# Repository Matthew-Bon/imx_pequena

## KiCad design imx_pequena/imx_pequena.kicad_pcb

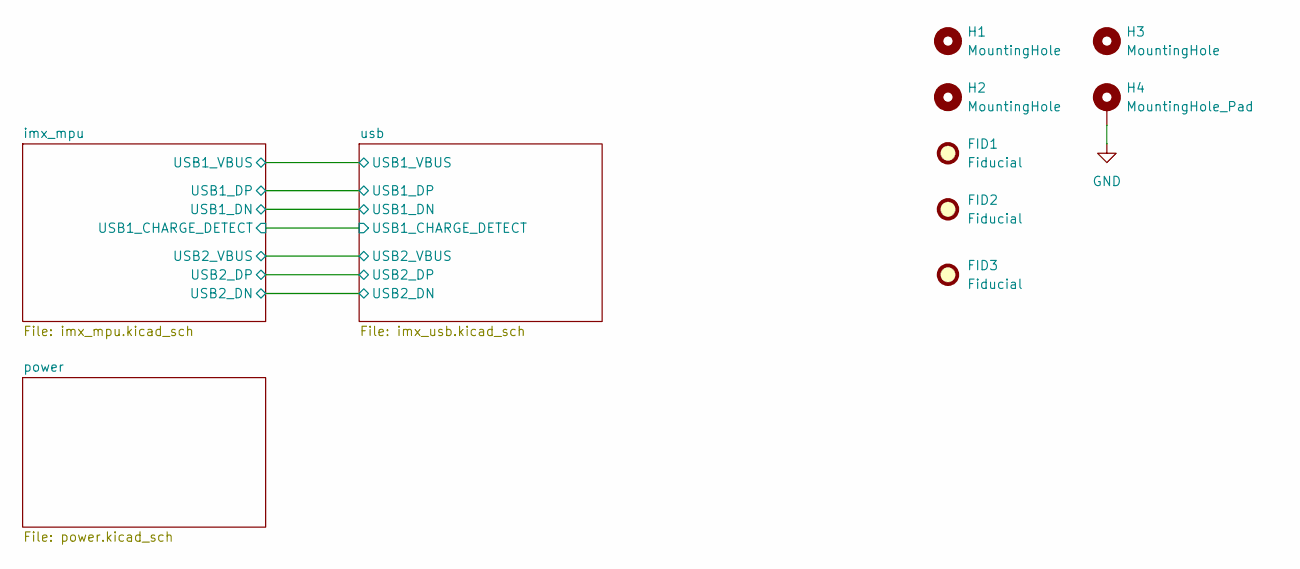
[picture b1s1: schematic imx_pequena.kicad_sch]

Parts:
FID1, FID2, FID3: Fiducial; Fiducial_1mm_Mask2mm
H1, H2, H3: MountingHole; MountingHole_2.5mm
H4: MountingHole_Pad; MountingHole_2.5mm_Pad

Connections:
GND: H4.1; also elsewhere on the board

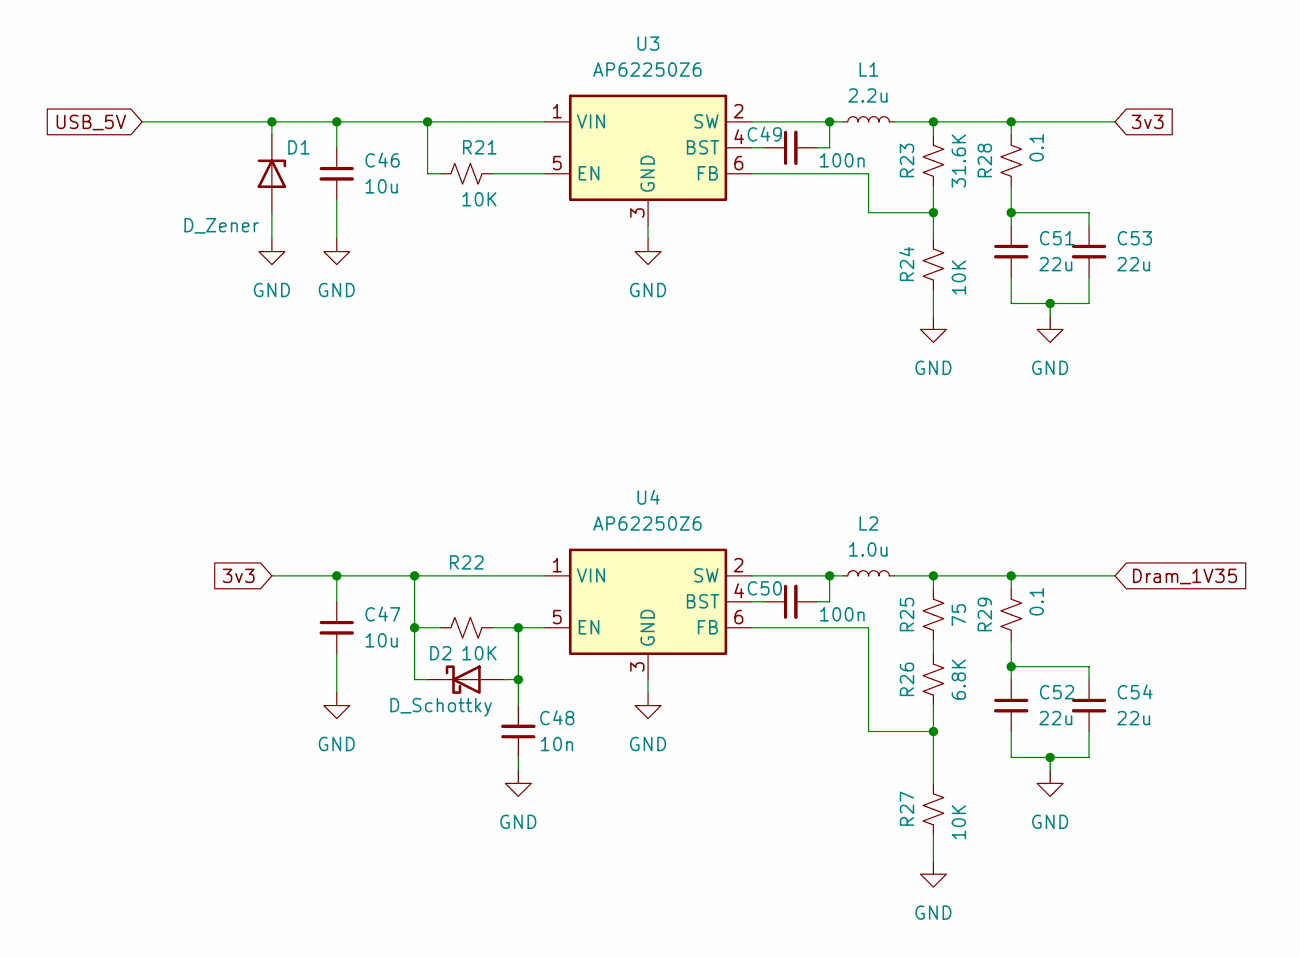
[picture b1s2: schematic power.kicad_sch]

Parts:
C46, C47: 10u; C_0805_2012Metric
C48: 10n; C_0805_2012Metric
C49, C50: 100n; C_0402_1005Metric
C51, C52, C53, C54: 22u; C_0805_2012Metric
D1: D_Zener; D_SOD-123
D2: D_Schottky; D_SOD-123
L1: 2.2u; L_Bourns_SRP5030T
L2: 1.0u; L_Bourns_SRP5030T
R21, R22, R24, R27: 10K; R_0402_1005Metric
R23: 31.6K; R_0402_1005Metric
R25: 75; R_0402_1005Metric
R26: 6.8K; R_0402_1005Metric
R28, R29: 0.1; R_0805_2012Metric
U3, U4: AP62250Z6; SOT-563

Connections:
3v3: C47.1, D2.1 (K), L1.2, R22.1, R23.2, R28.2, U4.1 (VIN); also elsewhere on the board
Dram_1V35: L2.2, R25.2, R29.2; also elsewhere on the board
GND: C46.2, C47.2, C48.1, C51.2, C52.2, C53.2, C54.2, D1.2 (A), R24.1, R27.1, U3.3 (GND), U4.3 (GND); also elsewhere on the board
unnamed: C48.2, D2.2 (A), R22.2, U4.5 (EN)
unnamed: C49.1, U3.4 (BST)
unnamed: C49.2, L1.1, U3.2 (SW)
unnamed: C50.1, U4.4 (BST)
unnamed: C50.2, L2.1, U4.2 (SW)
unnamed: C51.1, C53.1, R28.1
unnamed: C52.1, C54.1, R29.1
unnamed: R21.2, U3.5 (EN)
unnamed: R23.1, R24.2, U3.6 (FB)
unnamed: R25.1, R26.2
unnamed: R26.1, R27.2, U4.6 (FB)
USB_5V: C46.1, D1.1 (K), R21.1, U3.1 (VIN)

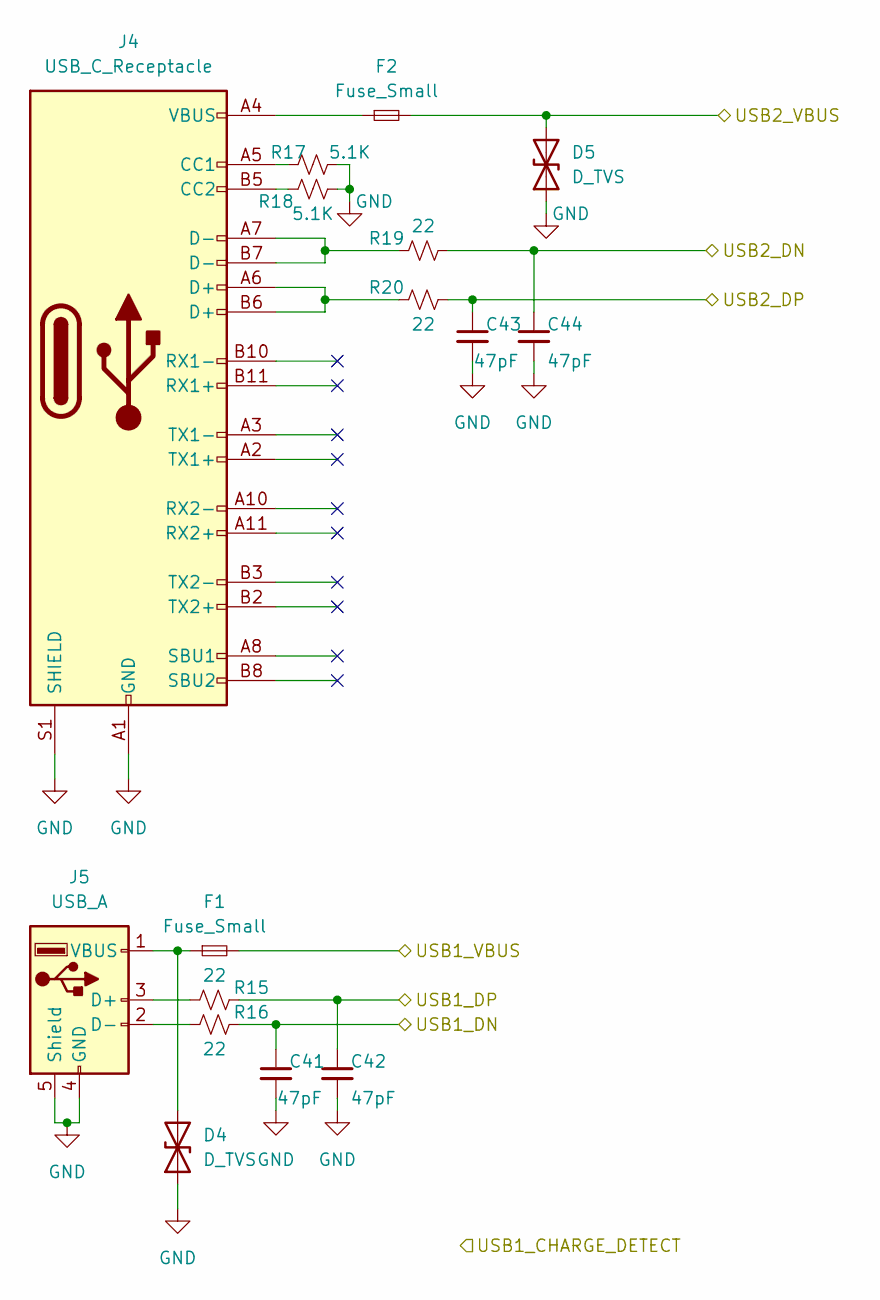
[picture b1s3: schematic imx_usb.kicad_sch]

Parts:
C41, C42, C43, C44: 47pF; C_0402_1005Metric
D4, D5: D_TVS; D_SOD-123
F1, F2: Fuse_Small; R_1206_3216Metric
J4: USB_C_Receptacle; USB_C_Receptacle_Amphenol_12401610E4-2A_CircularHoles
J5: USB_A; USB_A_Molex_67643_Horizontal
R15, R16, R19, R20: 22; R_0402_1005Metric
R17, R18: 5.1K; R_0402_1005Metric

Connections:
/imx_mpu/USB1_DN: C41.1, R16.2; also elsewhere on the board
/imx_mpu/USB1_DP: C42.1, R15.2; also elsewhere on the board
/imx_mpu/USB1_VBUS: F1.2; also elsewhere on the board
/imx_mpu/USB2_DN: C44.1, R19.2; also elsewhere on the board
/imx_mpu/USB2_DP: C43.1, R20.2; also elsewhere on the board
/imx_mpu/USB2_VBUS: D5.2 (A2), F2.2; also elsewhere on the board
GND: C41.2, C42.2, C43.2, C44.2, D4.1 (A1), D5.1 (A1), J4.A1 (GND), J4.A12 (GND), J4.B1 (GND), J4.B12 (GND), J4.S1 (SHIELD), J5.4 (GND), J5.5 (Shield), R17.2, R18.2; also elsewhere on the board
unnamed: D4.2 (A2), F1.1, J5.1 (VBUS)
unnamed: F2.1, J4.A4 (VBUS), J4.A9 (VBUS), J4.B4 (VBUS), J4.B9 (VBUS)
unnamed: J4.A5 (CC1), R17.1
unnamed: J4.A6 (D+), J4.B6 (D+), R20.1
unnamed: J4.A7 (D-), J4.B7 (D-), R19.1
unnamed: J4.B5 (CC2), R18.1
unnamed: J5.2 (D-), R16.1
unnamed: J5.3 (D+), R15.1

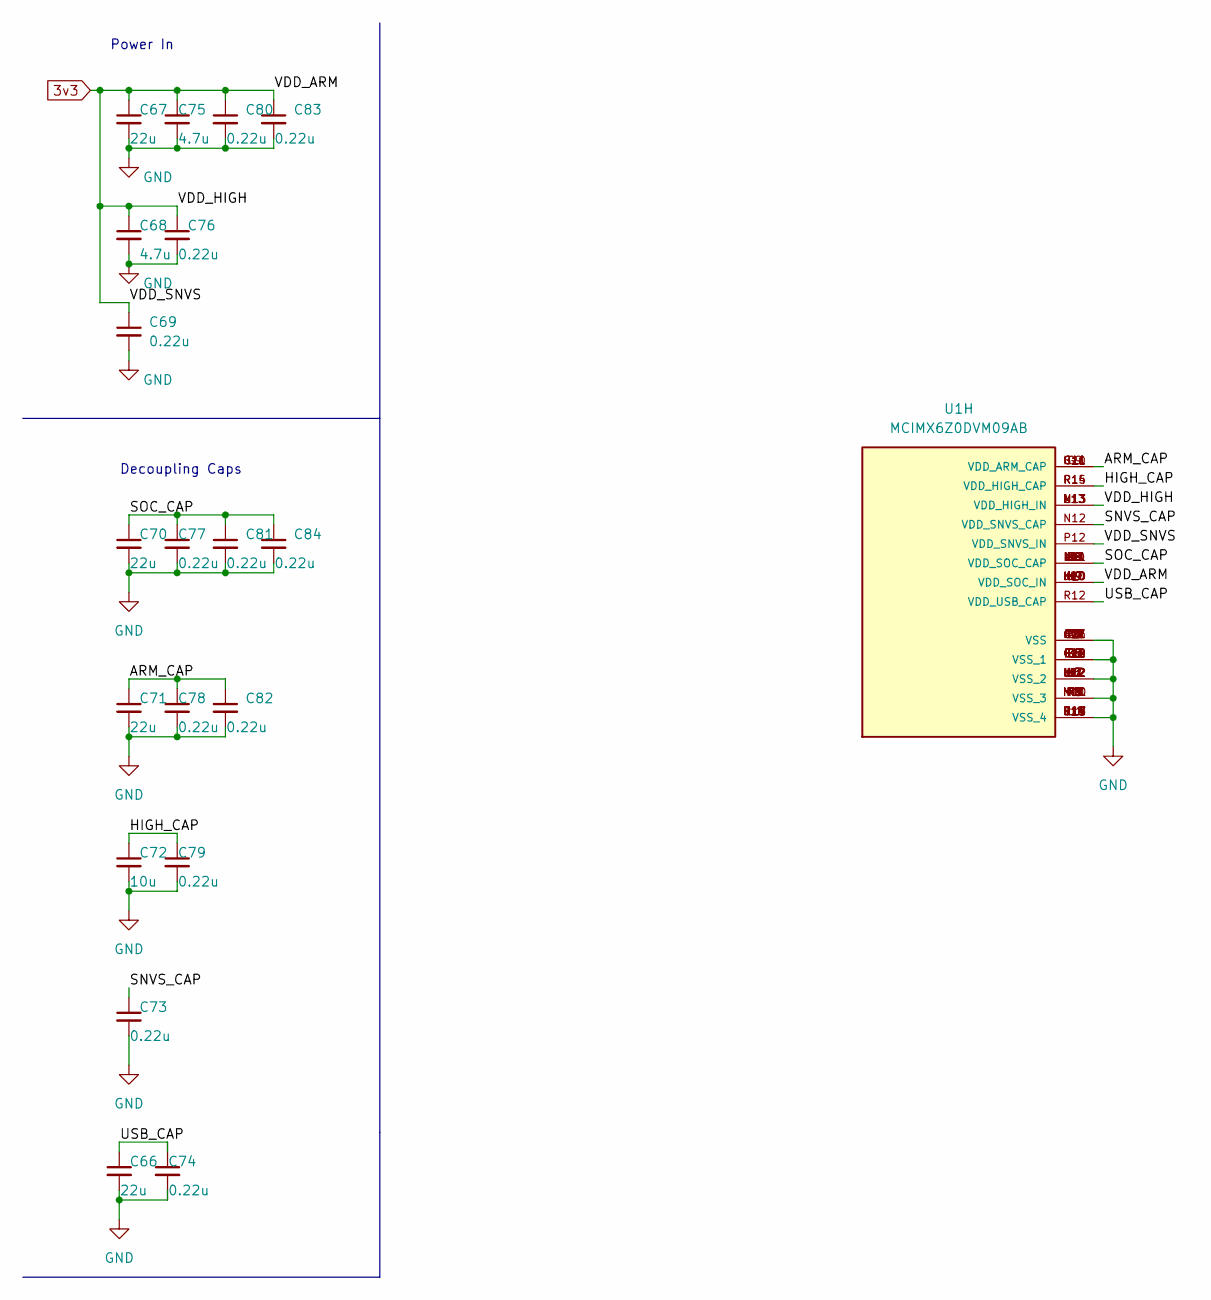
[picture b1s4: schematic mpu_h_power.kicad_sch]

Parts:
C66, C67, C70, C71: 22u; C_0805_2012Metric
C68, C75: 4.7u; C_0805_2012Metric
C69, C73, C74, C76, C77, C78, C79, C80, C81, C82, C83, C84: 0.22u; C_0402_1005Metric
C72: 10u; C_0805_2012Metric
U1: MCIMX6Z0DVM09AB; BGA289C80P17X17_1400X1400X132; PARTREV 0

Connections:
3v3: C67.1, C68.1, C69.1, C75.1, C76.1, C80.1, C83.1, U1.H9 (VDD_SOC_IN), U1.H10 (VDD_SOC_IN), U1.J9 (VDD_SOC_IN), U1.J10 (VDD_SOC_IN), U1.K9 (VDD_SOC_IN), U1.K10 (VDD_SOC_IN), U1.L13 (VDD_HIGH_IN), U1.M13 (VDD_HIGH_IN), U1.N13 (VDD_HIGH_IN), U1.P12 (VDD_SNVS_IN); also elsewhere on the board
/imx_mpu/mpu_h_power/ARM_CAP: C71.1, C78.1, C82.1, U1.G9 (VDD_ARM_CAP), U1.G10 (VDD_ARM_CAP), U1.G11 (VDD_ARM_CAP), U1.H11 (VDD_ARM_CAP)
/imx_mpu/mpu_h_power/HIGH_CAP: C72.1, C79.1, U1.R14 (VDD_HIGH_CAP), U1.R15 (VDD_HIGH_CAP)
/imx_mpu/mpu_h_power/SNVS_CAP: C73.1, U1.N12 (VDD_SNVS_CAP)
/imx_mpu/mpu_h_power/SOC_CAP: C70.1, C77.1, C81.1, C84.1, U1.G8 (VDD_SOC_CAP), U1.H8 (VDD_SOC_CAP), U1.J8 (VDD_SOC_CAP), U1.J11 (VDD_SOC_CAP), U1.K8 (VDD_SOC_CAP), U1.K11 (VDD_SOC_CAP), U1.L8 (VDD_SOC_CAP), U1.L9 (VDD_SOC_CAP), U1.L10 (VDD_SOC_CAP), U1.L11 (VDD_SOC_CAP)
/imx_mpu/mpu_h_power/USB_CAP: C66.1, C74.1, U1.R12 (VDD_USB_CAP)
GND: C66.2, C67.2, C68.2, C69.2, C70.2, C71.2, C72.2, C73.2, C74.2, C75.2, C76.2, C77.2, C78.2, C79.2, C80.2, C81.2, C82.2, C83.2, C84.2, U1.A1 (VSS), U1.A17 (VSS), U1.C3 (VSS), U1.C7 (VSS), U1.C11 (VSS), U1.C15 (VSS), U1.E8 (VSS), U1.E11 (VSS), U1.F6 (VSS), U1.F7 (VSS), U1.F8 (VSS_1), U1.F9 (VSS_1), U1.F10 (VSS_1), U1.F11 (VSS_1), U1.F12 (VSS_1), U1.G3 (VSS_1), U1.G5 (VSS_1), U1.G7 (VSS_1), U1.G12 (VSS_1), U1.G15 (VSS_1), U1.H7 (VSS_2), U1.H12 (VSS_2), U1.J5 (VSS_2), U1.J7 (VSS_2), U1.J12 (VSS_2), U1.K7 (VSS_2), U1.K12 (VSS_2), U1.L3 (VSS_2), U1.L7 (VSS_2), U1.L12 (VSS_2), U1.M7 (VSS_3), U1.M8 (VSS_3), U1.M9 (VSS_3), U1.M10 (VSS_3), U1.M11 (VSS_3), U1.N3 (VSS_3), U1.N5 (VSS_3), U1.R3 (VSS_3), U1.R5 (VSS_3), U1.R7 (VSS_3), U1.R11 (VSS_4), U1.R16 (VSS_4), U1.R17 (VSS_4), U1.T14 (VSS_4), U1.U1 (VSS_4), U1.U14 (VSS_4), U1.U17 (VSS_4); also elsewhere on the board

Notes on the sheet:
Power In
Decoupling Caps

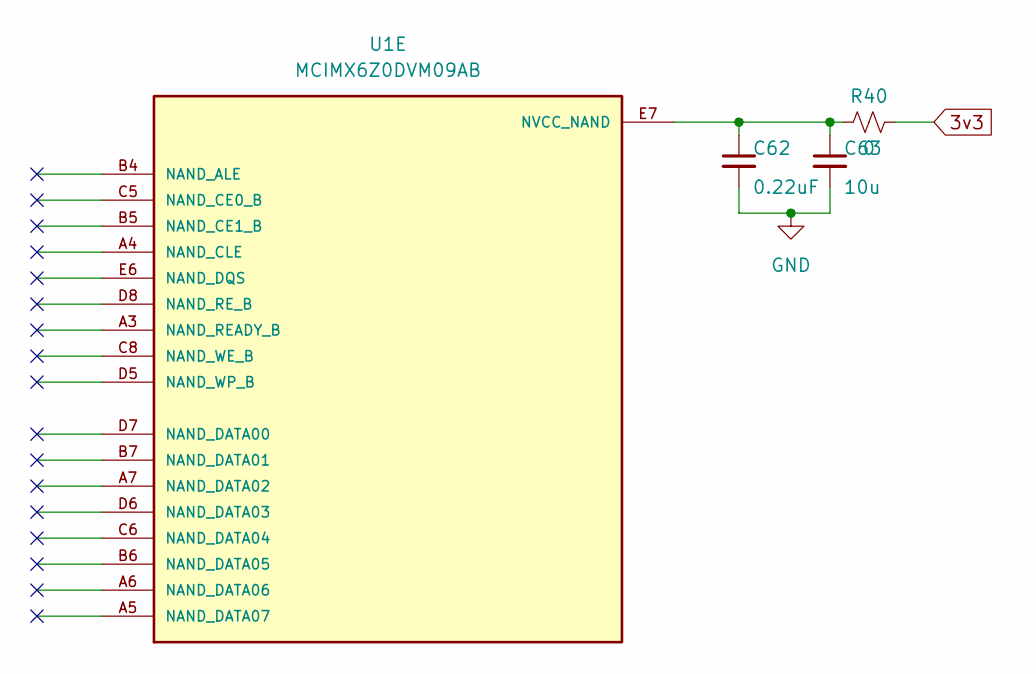
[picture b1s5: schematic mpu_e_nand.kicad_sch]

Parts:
C62: 0.22uF; C_0402_1005Metric
C63: 10u; C_0805_2012Metric
R40: 0; R_0402_1005Metric
U1: MCIMX6Z0DVM09AB; BGA289C80P17X17_1400X1400X132; PARTREV 0

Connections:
3v3: R40.2; also elsewhere on the board
GND: C62.2, C63.2; also elsewhere on the board
unnamed: C62.1, C63.1, R40.1, U1.E7 (NVCC_NAND)

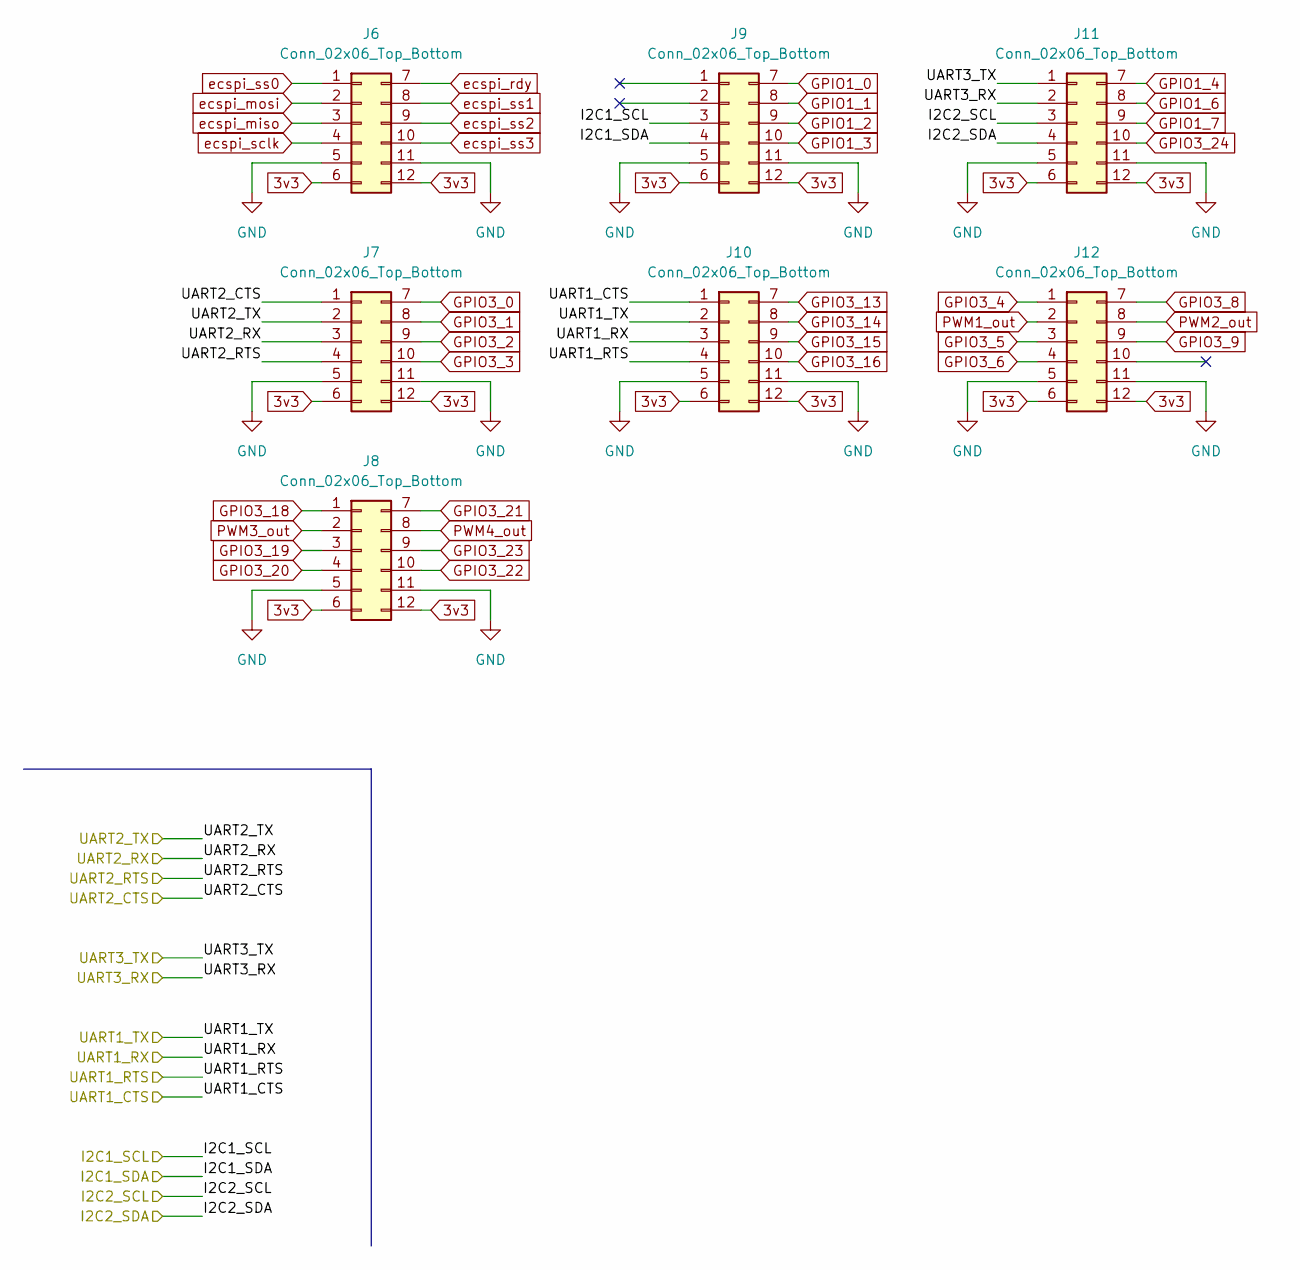
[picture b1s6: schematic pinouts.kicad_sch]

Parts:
J6, J7, J8, J9, J10, J11, J12: Conn_02x06_Top_Bottom; PinSocket_2x06_P2.54mm_Horizontal

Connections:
3v3: J6.6, J6.12, J7.6, J7.12, J8.6, J8.12, J9.6, J9.12, J10.6, J10.12, J11.6, J11.12, J12.6, J12.12; also elsewhere on the board
/imx_mpu/I2C1_SCL: J9.3; also elsewhere on the board
/imx_mpu/I2C1_SDA: J9.4; also elsewhere on the board
/imx_mpu/I2C2_SCL: J11.3; also elsewhere on the board
/imx_mpu/I2C2_SDA: J11.4; also elsewhere on the board
/imx_mpu/UART1_CTS: J10.1; also elsewhere on the board
/imx_mpu/UART1_RTS: J10.4; also elsewhere on the board
/imx_mpu/UART1_RX: J10.3; also elsewhere on the board
/imx_mpu/UART1_TX: J10.2; also elsewhere on the board
/imx_mpu/UART2_CTS: J7.1; also elsewhere on the board
/imx_mpu/UART2_RTS: J7.4; also elsewhere on the board
/imx_mpu/UART2_RX: J7.3; also elsewhere on the board
/imx_mpu/UART2_TX: J7.2; also elsewhere on the board
/imx_mpu/UART3_RX: J11.2; also elsewhere on the board
/imx_mpu/UART3_TX: J11.1; also elsewhere on the board
GND: J6.5, J6.11, J7.5, J7.11, J8.5, J8.11, J9.5, J9.11, J10.5, J10.11, J11.5, J11.11, J12.5, J12.11; also elsewhere on the board
GPIO1_0: J9.7; also elsewhere on the board
GPIO1_1: J9.8; also elsewhere on the board
GPIO1_2: J9.9; also elsewhere on the board
GPIO1_3: J9.10; also elsewhere on the board
GPIO1_4: J11.7; also elsewhere on the board
GPIO1_6: J11.8; also elsewhere on the board
GPIO1_7: J11.9; also elsewhere on the board
GPIO3_0: J7.7; also elsewhere on the board
GPIO3_1: J7.8; also elsewhere on the board
GPIO3_2: J7.9; also elsewhere on the board
GPIO3_3: J7.10; also elsewhere on the board
GPIO3_4: J12.1; also elsewhere on the board
GPIO3_5: J12.3; also elsewhere on the board
GPIO3_6: J12.4; also elsewhere on the board
GPIO3_8: J12.7; also elsewhere on the board
GPIO3_9: J12.9; also elsewhere on the board
GPIO3_13: J10.7; also elsewhere on the board
GPIO3_14: J10.8; also elsewhere on the board
GPIO3_15: J10.9; also elsewhere on the board
GPIO3_16: J10.10; also elsewhere on the board
GPIO3_18: J8.1; also elsewhere on the board
GPIO3_19: J8.3; also elsewhere on the board
GPIO3_20: J8.4; also elsewhere on the board
GPIO3_21: J8.7; also elsewhere on the board
GPIO3_22: J8.10; also elsewhere on the board
GPIO3_23: J8.9; also elsewhere on the board
GPIO3_24: J11.10; also elsewhere on the board
PWM1_out: J12.2; also elsewhere on the board
PWM2_out: J12.8; also elsewhere on the board
PWM3_out: J8.2; also elsewhere on the board
PWM4_out: J8.8; also elsewhere on the board
ecspi_miso: J6.3; also elsewhere on the board
ecspi_mosi: J6.2; also elsewhere on the board
ecspi_rdy: J6.7; also elsewhere on the board
ecspi_sclk: J6.4; also elsewhere on the board
ecspi_ss0: J6.1; also elsewhere on the board
ecspi_ss1: J6.8; also elsewhere on the board
ecspi_ss2: J6.9; also elsewhere on the board
ecspi_ss3: J6.10; also elsewhere on the board

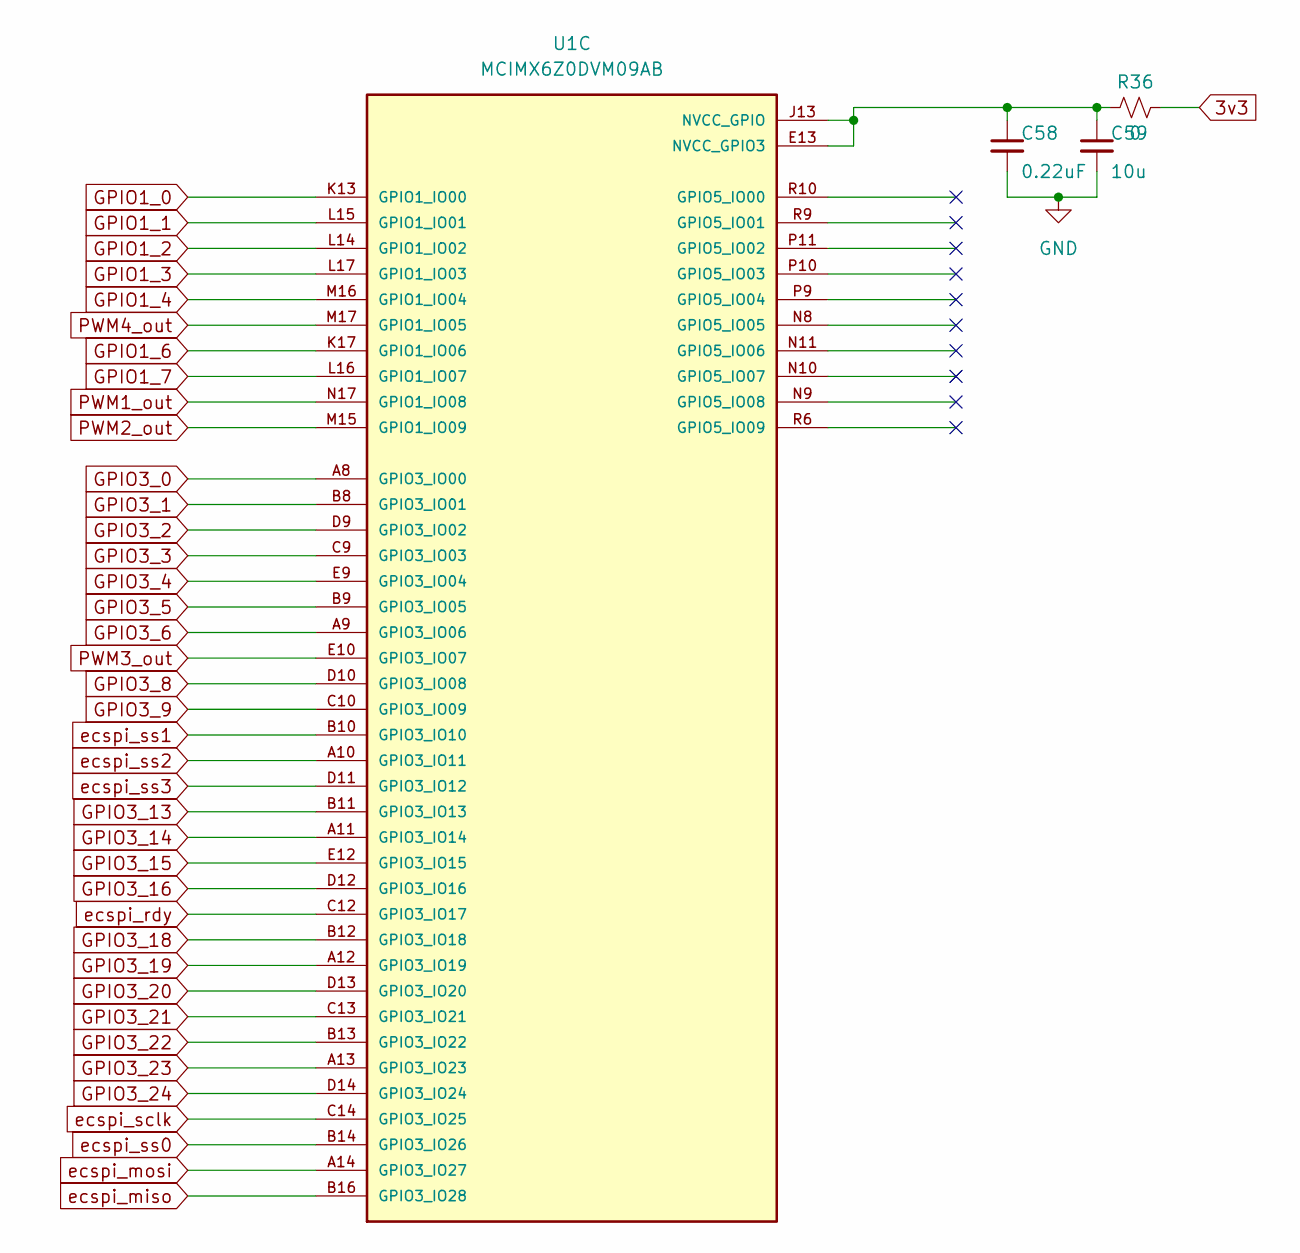
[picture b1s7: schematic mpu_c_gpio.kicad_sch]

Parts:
C58: 0.22uF; C_0402_1005Metric
C59: 10u; C_0805_2012Metric
R36: 0; R_0402_1005Metric
U1: MCIMX6Z0DVM09AB; BGA289C80P17X17_1400X1400X132; PARTREV 0

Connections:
3v3: R36.2; also elsewhere on the board
GND: C58.2, C59.2; also elsewhere on the board
GPIO1_0: U1.K13 (GPIO1_IO00); also elsewhere on the board
GPIO1_1: U1.L15 (GPIO1_IO01); also elsewhere on the board
GPIO1_2: U1.L14 (GPIO1_IO02); also elsewhere on the board
GPIO1_3: U1.L17 (GPIO1_IO03); also elsewhere on the board
GPIO1_4: U1.M16 (GPIO1_IO04); also elsewhere on the board
GPIO1_6: U1.K17 (GPIO1_IO06); also elsewhere on the board
GPIO1_7: U1.L16 (GPIO1_IO07); also elsewhere on the board
GPIO3_0: U1.A8 (GPIO3_IO00); also elsewhere on the board
GPIO3_1: U1.B8 (GPIO3_IO01); also elsewhere on the board
GPIO3_2: U1.D9 (GPIO3_IO02); also elsewhere on the board
GPIO3_3: U1.C9 (GPIO3_IO03); also elsewhere on the board
GPIO3_4: U1.E9 (GPIO3_IO04); also elsewhere on the board
GPIO3_5: U1.B9 (GPIO3_IO05); also elsewhere on the board
GPIO3_6: U1.A9 (GPIO3_IO06); also elsewhere on the board
GPIO3_8: U1.D10 (GPIO3_IO08); also elsewhere on the board
GPIO3_9: U1.C10 (GPIO3_IO09); also elsewhere on the board
GPIO3_13: U1.B11 (GPIO3_IO13); also elsewhere on the board
GPIO3_14: U1.A11 (GPIO3_IO14); also elsewhere on the board
GPIO3_15: U1.E12 (GPIO3_IO15); also elsewhere on the board
GPIO3_16: U1.D12 (GPIO3_IO16); also elsewhere on the board
GPIO3_18: U1.B12 (GPIO3_IO18); also elsewhere on the board
GPIO3_19: U1.A12 (GPIO3_IO19); also elsewhere on the board
GPIO3_20: U1.D13 (GPIO3_IO20); also elsewhere on the board
GPIO3_21: U1.C13 (GPIO3_IO21); also elsewhere on the board
GPIO3_22: U1.B13 (GPIO3_IO22); also elsewhere on the board
GPIO3_23: U1.A13 (GPIO3_IO23); also elsewhere on the board
GPIO3_24: U1.D14 (GPIO3_IO24); also elsewhere on the board
unnamed: C58.1, C59.1, R36.1, U1.E13 (NVCC_GPIO3), U1.J13 (NVCC_GPIO)
PWM1_out: U1.N17 (GPIO1_IO08); also elsewhere on the board
PWM2_out: U1.M15 (GPIO1_IO09); also elsewhere on the board
PWM3_out: U1.E10 (GPIO3_IO07); also elsewhere on the board
PWM4_out: U1.M17 (GPIO1_IO05); also elsewhere on the board
ecspi_miso: U1.B16 (GPIO3_IO28); also elsewhere on the board
ecspi_mosi: U1.A14 (GPIO3_IO27); also elsewhere on the board
ecspi_rdy: U1.C12 (GPIO3_IO17); also elsewhere on the board
ecspi_sclk: U1.C14 (GPIO3_IO25); also elsewhere on the board
ecspi_ss0: U1.B14 (GPIO3_IO26); also elsewhere on the board
ecspi_ss1: U1.B10 (GPIO3_IO10); also elsewhere on the board
ecspi_ss2: U1.A10 (GPIO3_IO11); also elsewhere on the board
ecspi_ss3: U1.D11 (GPIO3_IO12); also elsewhere on the board

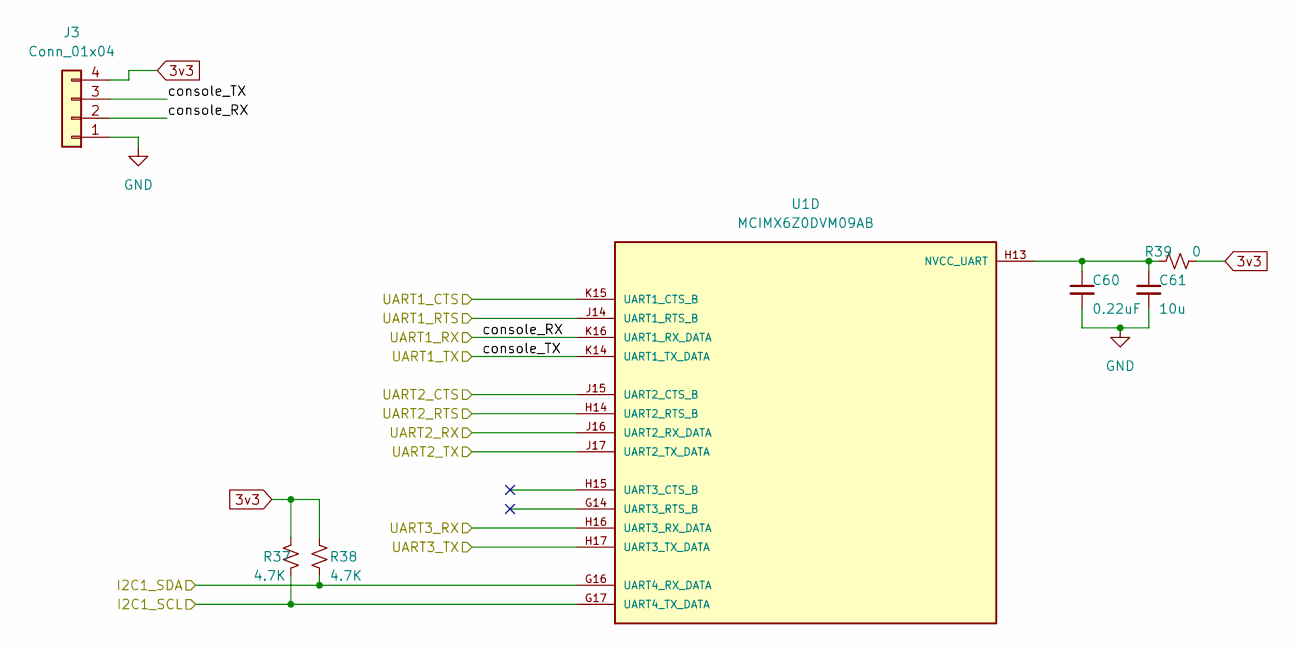
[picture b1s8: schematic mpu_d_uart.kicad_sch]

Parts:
C60: 0.22uF; C_0402_1005Metric
C61: 10u; C_0805_2012Metric
J3: Conn_01x04; PinHeader_1x04_P2.54mm_Vertical
R37, R38: 4.7K; R_0402_1005Metric
R39: 0; R_0402_1005Metric
U1: MCIMX6Z0DVM09AB; BGA289C80P17X17_1400X1400X132; PARTREV 0

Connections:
3v3: J3.4, R37.1, R38.1, R39.2; also elsewhere on the board
/imx_mpu/I2C1_SCL: R37.2, U1.G17 (UART4_TX_DATA); also elsewhere on the board
/imx_mpu/I2C1_SDA: R38.2, U1.G16 (UART4_RX_DATA); also elsewhere on the board
/imx_mpu/UART1_CTS: U1.J14 (UART1_RTS_B); also elsewhere on the board
/imx_mpu/UART1_RTS: U1.K15 (UART1_CTS_B); also elsewhere on the board
/imx_mpu/UART1_RX: J3.2, U1.K16 (UART1_RX_DATA); also elsewhere on the board
/imx_mpu/UART1_TX: J3.3, U1.K14 (UART1_TX_DATA); also elsewhere on the board
/imx_mpu/UART2_CTS: U1.J15 (UART2_CTS_B); also elsewhere on the board
/imx_mpu/UART2_RTS: U1.H14 (UART2_RTS_B); also elsewhere on the board
/imx_mpu/UART2_RX: U1.J16 (UART2_RX_DATA); also elsewhere on the board
/imx_mpu/UART2_TX: U1.J17 (UART2_TX_DATA); also elsewhere on the board
/imx_mpu/UART3_RX: U1.H16 (UART3_RX_DATA); also elsewhere on the board
/imx_mpu/UART3_TX: U1.H17 (UART3_TX_DATA); also elsewhere on the board
GND: C60.2, C61.2, J3.1; also elsewhere on the board
unnamed: C60.1, C61.1, R39.1, U1.H13 (NVCC_UART)

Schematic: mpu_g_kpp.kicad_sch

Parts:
C64: 0.22uF; C_0402_1005Metric
C65: 10u; C_0805_2012Metric
R42: 0; R_0402_1005Metric
U1: MCIMX6Z0DVM09AB; BGA289C80P17X17_1400X1400X132; PARTREV 0

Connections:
3v3: R42.2; also elsewhere on the board
GND: C64.2, C65.2; also elsewhere on the board
unnamed: C64.1, C65.1, R42.1, U1.F13 (NVCC_KPP)

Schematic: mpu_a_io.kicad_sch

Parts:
C1, C5, C6: 1u; C_0603_1608Metric
C3, C4: 15p; C_0402_1005Metric
C45: DNP; C_0402_1005Metric
C55: DNP; C_0805_2012Metric
C56: 0.22uF; C_0402_1005Metric
C57: 10u; C_0805_2012Metric
D3: D_Schottky; D_SOD-123
J1: Conn_ARM_JTAG_SWD_10; PinHeader_2x05_P1.27mm_Vertical
R1, R2: 4.7K; R_0402_1005Metric
R30, R31: 10K; R_0402_1005Metric
R32: DNI; R_0402_1005Metric
R33, R34: 0; R_0402_1005Metric
R35: DNP; R_0402_1005Metric
SW1, SW2: SW_SPST; SW_SPST_TL3342
TP1: Bootmode 0; TestPoint_Pad_1.0x1.0mm
TP2: Bootmode 1; TestPoint_Pad_1.0x1.0mm
TP3: SNVS; TestPoint_Pad_1.0x1.0mm
U1: MCIMX6Z0DVM09AB; BGA289C80P17X17_1400X1400X132; PARTREV 0
X1: ASE-xxxMHz; Oscillator_SMD_Abracon_ASE-4Pin_3.2x2.5mm
Y2: Crystal; Crystal_SMD_MicroCrystal_MS1V-T1K

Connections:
3v3: C1.1, D3.2 (A), R1.1, R2.1, R30.1, R31.1, R32.2, R34.2, R35.1, X1.1 (EN), X1.4 (Vdd); also elsewhere on the board
/imx_mpu/I2C2_SCL: R2.2, U1.F17 (I2C2_SCL); also elsewhere on the board
/imx_mpu/I2C2_SDA: R1.2, U1.G13 (I2C2_SDA); also elsewhere on the board
/imx_mpu/USB1_CHARGE_DETECT: U1.U16 (USB_OTG1_CHD_B)
/imx_mpu/USB1_DN: U1.T15 (USB_OTG1_DN); also elsewhere on the board
/imx_mpu/USB1_DP: U1.U15 (USB_OTG1_DP); also elsewhere on the board
/imx_mpu/USB1_VBUS: C6.1, U1.T12 (USB_OTG1_VBUS); also elsewhere on the board
/imx_mpu/USB2_DN: U1.T13 (USB_OTG2_DN); also elsewhere on the board
/imx_mpu/USB2_DP: U1.U13 (USB_OTG2_DP); also elsewhere on the board
/imx_mpu/USB2_VBUS: C5.1, U1.U12 (USB_OTG2_VBUS); also elsewhere on the board
/imx_mpu/mpu_a_io/JTAG_RESET: J1.10 (~RESET), U1.N14 (JTAG_TRST_B)
/imx_mpu/mpu_a_io/TCK: J1.4 (SWDCLK/TCK), U1.M14 (JTAG_TCK)
/imx_mpu/mpu_a_io/TDI: J1.8 (NC/TDI), U1.N16 (JTAG_TDI)
/imx_mpu/mpu_a_io/TDO: J1.6 (SWO/TDO), U1.N15 (JTAG_TDO)
/imx_mpu/mpu_a_io/TMS: J1.2 (SWDIO/TMS), U1.P14 (JTAG_TMS)
/imx_mpu/mpu_a_io/~ONOFF: C55.1, R31.2, SW2.2 (B), U1.R8 (ONOFF)
/imx_mpu/mpu_a_io/~Reset: C45.1, R30.2, SW1.2 (B), U1.P8 (POR_B)
GND: C1.2, C3.2, C4.2, C5.2, C6.2, C45.2, C55.2, C56.2, C57.2, J1.3 (GND), J1.5 (GND), J1.9 (GNDDetect), R33.1, SW1.1 (A), SW2.1 (A), U1.M12 (NGND_KEL0), U1.N7 (TEST_MODE), X1.2 (GND); also elsewhere on the board
unnamed: C3.1, U1.T11 (RTC_XTALI), Y2.1
unnamed: C4.1, U1.U11 (RTC_XTALO), Y2.2
unnamed: C56.1, C57.1, R34.1, U1.P13 (NVCC_PLL)
unnamed: D3.1 (K), J1.1 (VTref), R35.2
unnamed: R32.1, R33.2, U1.P15 (JTAG_MOD)
unnamed: TP1.1, U1.T10 (BOOT_MODE0)
unnamed: TP2.1, U1.U10 (BOOT_MODE1)
unnamed: TP3.1, U1.T9 (SNVS_PMIC_ON_REQ)
unnamed: U1.T17 (XTALO), X1.3 (OUT)

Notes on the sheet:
SG-3031CM 32.7680KB3

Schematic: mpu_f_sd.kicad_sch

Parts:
C18: 0.1u; C_0402_1005Metric
C19: 22u; C_0805_2012Metric
C20, C21: 0.22u; C_0402_1005Metric
J2: Micro_SD_Card; microSD_HC_Hirose_DM3AT-SF-PEJM5
R9, R10, R11, R12, R13, R14: 10K; R_0402_1005Metric
R41: 0; R_0402_1005Metric
U1: MCIMX6Z0DVM09AB; BGA289C80P17X17_1400X1400X132; PARTREV 0

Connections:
3v3: R41.2; also elsewhere on the board
/imx_mpu/mpu_f_sd/SD_3v3: C18.1, C19.1, C20.1, C21.1, J2.4 (VDD), R9.1, R10.1, R11.1, R12.1, R13.1, R14.1, R41.1, U1.C4 (NVCC_SD1), U1.F4 (NVCC_SD2)
/imx_mpu/mpu_f_sd/SD_CLK: J2.5 (CLK), R9.2, U1.C1 (SD1_CLK)
/imx_mpu/mpu_f_sd/SD_CMD: J2.3 (CMD), R10.2, U1.C2 (SD1_CMD)
/imx_mpu/mpu_f_sd/SD_DATA0: J2.7 (DAT0), R11.2, U1.B3 (SD1_DATA0)
/imx_mpu/mpu_f_sd/SD_DATA1: J2.8 (DAT1), R12.2, U1.B2 (SD1_DATA1)
/imx_mpu/mpu_f_sd/SD_DATA2: J2.1 (DAT2), R13.2, U1.B1 (SD1_DATA2)
/imx_mpu/mpu_f_sd/SD_DATA3: J2.2 (DAT3/CD), R14.2, U1.A2 (SD1_DATA3)
GND: C18.2, C19.2, C20.2, C21.2, J2.6 (VSS), J2.9 (SHIELD); also elsewhere on the board

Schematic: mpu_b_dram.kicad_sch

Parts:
C7: 4.7u; C_0603_1608Metric
C8, C9: 0.1u; C_0402_1005Metric
C10, C11, C12, C13: 0.22u; C_0402_1005Metric
C14, C15: DNP; C_0402_1005Metric
C16, C17: 2.2p; C_0402_1005Metric
R3, R4: 1.5K; R_0402_1005Metric
R5, R7: 240; R_0402_1005Metric
R6: 10K; R_0402_1005Metric
R8: 470; R_0402_1005Metric
U1: MCIMX6Z0DVM09AB; BGA289C80P17X17_1400X1400X132; PARTREV 0
U2: MT41K64M16TW-107:J_TR; BGA96C80P9X16_1400X800X120N; PARTREV Rev. L EN 9/18

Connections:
/imx_mpu/mpu_b_dram/DAT00: U1.T4 (DRAM_DATA00), U2.E3 (DQ0)
/imx_mpu/mpu_b_dram/DAT01: U1.U6 (DRAM_DATA01), U2.F7 (DQ1)
/imx_mpu/mpu_b_dram/DAT02: U1.T6 (DRAM_DATA02), U2.F2 (DQ2)
/imx_mpu/mpu_b_dram/DAT03: U1.U7 (DRAM_DATA03), U2.F8 (DQ3)
/imx_mpu/mpu_b_dram/DAT04: U1.U8 (DRAM_DATA04), U2.H3 (DQ4)
/imx_mpu/mpu_b_dram/DAT05: U1.T8 (DRAM_DATA05), U2.H8 (DQ5)
/imx_mpu/mpu_b_dram/DAT06: U1.T5 (DRAM_DATA06), U2.G2 (DQ6)
/imx_mpu/mpu_b_dram/DAT07: U1.U4 (DRAM_DATA07), U2.H7 (DQ7)
/imx_mpu/mpu_b_dram/DAT08: U1.U2 (DRAM_DATA08), U2.D7 (DQ8)
/imx_mpu/mpu_b_dram/DAT09: U1.U3 (DRAM_DATA09), U2.C3 (DQ9)
/imx_mpu/mpu_b_dram/DAT10: U1.U5 (DRAM_DATA10), U2.C8 (DQ10)
/imx_mpu/mpu_b_dram/DAT11: U1.R4 (DRAM_DATA11), U2.C2 (DQ11)
/imx_mpu/mpu_b_dram/DAT12: U1.P5 (DRAM_DATA12), U2.A7 (DQ12)
/imx_mpu/mpu_b_dram/DAT13: U1.P3 (DRAM_DATA13), U2.A2 (DQ13)
/imx_mpu/mpu_b_dram/DAT14: U1.R2 (DRAM_DATA14), U2.B8 (DQ14)
/imx_mpu/mpu_b_dram/DAT15: U1.R1 (DRAM_DATA15), U2.A3 (DQ15)
/imx_mpu/mpu_b_dram/DRAM_BA0: U1.M1 (DRAM_SDBA0), U2.M2 (BA0)
/imx_mpu/mpu_b_dram/DRAM_BA1: U1.H1 (DRAM_SDBA1), U2.N8 (BA1)
/imx_mpu/mpu_b_dram/DRAM_BA2: U1.K2 (DRAM_SDBA2), U2.M3 (BA2)
/imx_mpu/mpu_b_dram/DRAM_CAS: U1.J2 (DRAM_CAS_B), U2.K3 (CAS#)
/imx_mpu/mpu_b_dram/DRAM_CKE: U1.M3 (DRAM_SDCKE0), U2.K9 (CKE)
/imx_mpu/mpu_b_dram/DRAM_CS0: U1.N2 (DRAM_CS0_B), U2.L2 (CS#)
/imx_mpu/mpu_b_dram/DRAM_LDM: U1.T7 (DRAM_DQM0), U2.E7 (LDM)
/imx_mpu/mpu_b_dram/DRAM_ODT: U1.N1 (DRAM_ODT0), U2.K1 (ODT)
/imx_mpu/mpu_b_dram/DRAM_RAS: U1.M5 (DRAM_RAS_B), U2.J3 (RAS#)
/imx_mpu/mpu_b_dram/DRAM_RESET: R6.1, U1.G4 (DRAM_RESET), U2.T2 (RESET#)
/imx_mpu/mpu_b_dram/DRAM_SDCLK0_N: R8.2, U1.P2 (DRAM_SDCLK0_N), U2.K7 (CK#)
/imx_mpu/mpu_b_dram/DRAM_SDCLK0_P: R8.1, U1.P1 (DRAM_SDCLK0_P), U2.J7 (CK)
/imx_mpu/mpu_b_dram/DRAM_SDQS0_N: C15.2, C17.2, U1.P7 (DRAM_SDQS0_N), U2.G3 (LDQS#)
/imx_mpu/mpu_b_dram/DRAM_SDQS0_P: C15.1, C17.1, U1.P6 (DRAM_SDQS0_P), U2.F3 (LDQS)
/imx_mpu/mpu_b_dram/DRAM_SDQS1_N: C14.2, C16.2, U1.T2 (DRAM_SDQS1_N), U2.B7 (UDQS#)
/imx_mpu/mpu_b_dram/DRAM_SDQS1_P: C14.1, C16.1, U1.T1 (DRAM_SDQS1_P), U2.C7 (UDQS)
/imx_mpu/mpu_b_dram/DRAM_UDM: U1.T3 (DRAM_DQM1), U2.D3 (UDM)
/imx_mpu/mpu_b_dram/DRAM_WE: U1.J1 (DRAM_SDWE_B), U2.L3 (WE#)
/imx_mpu/mpu_b_dram/Dram_vref: C8.2, C9.1, C10.1, C11.1, C12.1, R3.2, R4.1, U1.P4 (DRAM_VREF), U2.H1 (VREFDQ), U2.M8 (VREFCA)
Dram_1V35: C7.1, C8.1, R3.1, U1.G6 (NVCC_DRAM), U1.H6 (NVCC_DRAM), U1.J6 (NVCC_DRAM), U1.K6 (NVCC_DRAM), U1.L6 (NVCC_DRAM), U1.M6 (NVCC_DRAM), U2.A1 (VDDQ), U2.A8 (VDDQ), U2.B2 (VDD), U2.C1 (VDDQ), U2.C9 (VDDQ), U2.D2 (VDDQ), U2.D9 (VDD), U2.E9 (VDDQ), U2.F1 (VDDQ), U2.G7 (VDD), U2.H2 (VDDQ), U2.H9 (VDDQ), U2.K2 (VDD), U2.K8 (VDD), U2.N1 (VDD), U2.N9 (VDD), U2.R1 (VDD), U2.R9 (VDD); also elsewhere on the board
GND: C7.2, C9.2, C10.2, C11.2, C12.2, C13.2, R4.2, R5.2, R6.2, R7.2, U2.A9 (VSS), U2.B1 (VSSQ), U2.B3 (VSS), U2.B9 (VSSQ), U2.D1 (VSSQ), U2.D8 (VSSQ), U2.E1 (VSS), U2.E2 (VSSQ), U2.E8 (VSSQ), U2.F9 (VSSQ), U2.G1 (VSSQ), U2.G8 (VSS), U2.G9 (VSSQ), U2.J2 (VSS), U2.J8 (VSS), U2.M1 (VSS), U2.M9 (VSS), U2.P1 (VSS), U2.P9 (VSS), U2.T1 (VSS), U2.T9 (VSS); also elsewhere on the board
unnamed: R5.1, U1.N4 (DRAM_ZQPAD)
unnamed: R7.1, U2.L8 (ZQ)
unnamed: U1.G2 (DRAM_ADDR06), U2.R8 (A6)
unnamed: U1.H2 (DRAM_ADDR01), U2.P7 (A1)
unnamed: U1.H4 (DRAM_ADDR07), U2.R2 (A7)
unnamed: U1.J4 (DRAM_ADDR08), U2.T8 (A8)
unnamed: U1.K1 (DRAM_ADDR02), U2.P3 (A2)
unnamed: U1.K3 (DRAM_ADDR11), U2.R7 (A11)
unnamed: U1.K4 (DRAM_ADDR04), U2.P8 (A4)
unnamed: U1.L1 (DRAM_ADDR05), U2.P2 (A5)
unnamed: U1.L2 (DRAM_ADDR09), U2.R3 (A9)
unnamed: U1.L4 (DRAM_ADDR12), U2.N7 (A12/BC#)
unnamed: U1.L5 (DRAM_ADDR00), U2.N3 (A0)
unnamed: U1.M2 (DRAM_ADDR03), U2.N2 (A3)
unnamed: U1.M4 (DRAM_ADDR10), U2.L7 (A10/AP)
VDD_HIGH_CAP: C13.1, U1.N6 (NVCC_DRAM_2P5)

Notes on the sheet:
Place 0.22us near DRAM pins
Place Near DRAM
DRAM VREF

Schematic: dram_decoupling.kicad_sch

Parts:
C22: 22u; C_0805_2012Metric
C23, C25, C26, C27, C28, C29, C30, C31, C32, C33, C34, C35, C36, C37, C38, C39, C40: 0.22u; C_0402_1005Metric
C24: 10u; C_0805_2012Metric

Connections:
Dram_1V35: C22.1, C23.1, C24.1, C25.1, C26.1, C27.1, C28.1, C29.1, C30.1, C31.1, C32.1, C33.1, C34.1, C35.1, C36.1, C37.1, C38.1, C39.1, C40.1; also elsewhere on the board
GND: C22.2, C23.2, C24.2, C25.2, C26.2, C27.2, C28.2, C29.2, C30.2, C31.2, C32.2, C33.2, C34.2, C35.2, C36.2, C37.2, C38.2, C39.2, C40.2; also elsewhere on the board

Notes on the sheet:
BULK DECOUPLING
